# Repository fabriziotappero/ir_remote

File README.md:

# Camera Infrared Remote Control
This repository contains the hardware and software implementation of a infrared 
remote control based on the [Espressif ESP32 module]. This module allow to remotely
control any infrared camera like, in my case, the Sony NEX6 camera.

Notice how an IR reader (U3) can be used to program the ESP32 so that the same
remote can actually control any given camera. 

The schematic and PCB was designed using de EDA tool [KiCad] and all C++ 
code was compiled using the [Espressif ESP32 toolchain].

## Electronic Schematic
![][ir_remote_sch]

[ir_remote_sch]: https://github.com/fabriziotappero/ir_remote/blob/master/PCB/ir_remote_sch.png ""
[Espressif ESP32 module]: https://www.espressif.com/en/products/hardware/development-boards
[Espressif ESP32 toolchain]: https://dl.espressif.com/doc/esp-idf/latest/index.html
[KiCad]: http://kicad-pcb.org/

## Printed Circuit Board
This is the 2 layer PCB designed to sit on top of a ESP32 evaluation board. Notice the castellated
mounting holes.

![][ir_remote_pcb]

[ir_remote_pcb]: https://github.com/fabriziotappero/ir_remote/blob/master/PCB/ir_remote_pcb.png ""

## Hardware And Software Tools

Install **Kicad 5** on Debial-like Linux systems:
```
sudo add-apt-repository --yes ppa:js-reynaud/kicad-5
sudo apt-get update
sudo apt-get install kicad kicad-libraries
```

Install **ESP32 Espressif** compiler with its dependencies:
```
sudo apt-get install git wget make libncurses-dev flex bison gperf python python-serial

wget https://dl.espressif.com/dl/xtensa-esp32-elf-linux64-1.22.0-80-g6c4433a-5.2.0.tar.gz

tar -xvf xtensa-esp32-elf-linux64-1.22.0-80-g6c4433a-5.2.0.tar.gz
sudo mv xtensa-esp32-elf /opt
export PATH=/opt/xtensa-esp32-elf/bin:$PATH
```
Install the **ESP32 Espressif** developing environment IDF:
```
mkdir /opt/eps32 
cd /opt/eps32
git clone --recursive https://github.com/espressif/esp-idf.git
cd esp-idf
git submodule update --init
export IDF_PATH=/opt/esp32/esp-idf
```

Begin from a simple example:
```
git clone https://github.com/espressif/esp-idf-template.git myapp
cd myapp
make menuconfig
make flash
```
A lot of code examples in ```/opt/esp32/esp-idf/examples```. For more information refer to the [Espressif ESP32 Programming Guide]

[Espressif ESP32 Programming Guide]: https://dl.espressif.com/doc/esp-idf/latest/index.html

## References

[Espressif ESP32 Programming Guide](https://dl.espressif.com/doc/esp-idf/latest/index.html)

## More Information
For any enquiry contact:

fabrizio.tappero@gmail.com

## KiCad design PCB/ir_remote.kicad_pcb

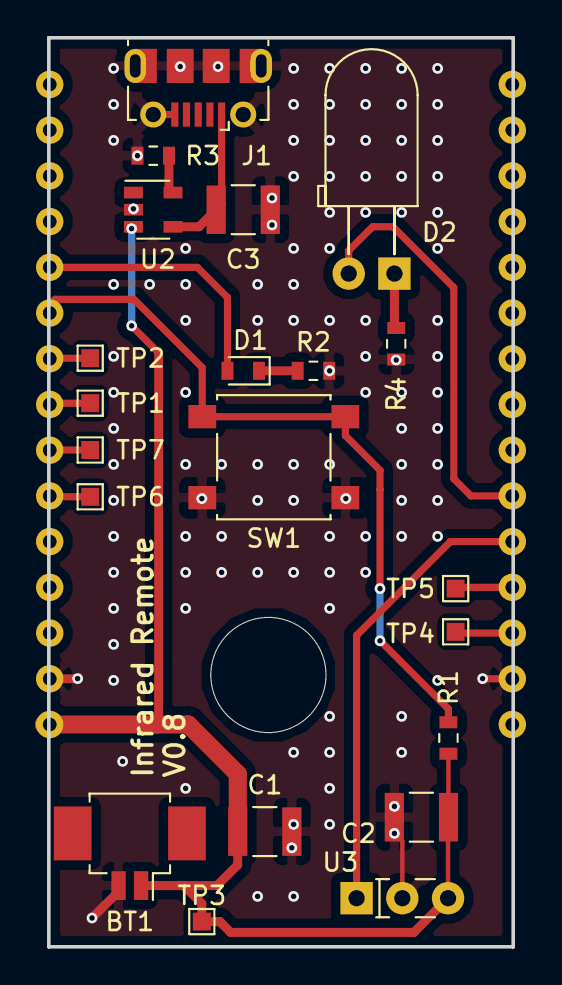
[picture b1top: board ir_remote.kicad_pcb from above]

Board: 2 copper layers, 25.8 x 50.5 mm, 22 parts (1 on the bottom side), 16 nets.

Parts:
BT1: SM02B-SRSS-TB (LF)(SN); Molex_PicoBlade_53261-0271_1x02_P1.25mm_Horizontal
C1, C2, C3: 4.7uF; C_1210_3225Metric
D1: APTD1608LCGCK; LED_0603_1608Metric
D2: 15400394A3590; LED_D5.0mm_Horizontal_O3.81mm_Z3.0mm
J1: 105017-0001; USB_Micro-B_Molex-105017-0001
R1: 10k; R_0603_1608Metric
R2, R3: 2k; R_0603_1608Metric
R4: 120R; R_0603_1608Metric
SW1: 95C06B3GWRT; SW_SPST_B3S-1000
TP1, TP2, TP3, TP4, TP5, TP6, TP7: Test_Point; TestPoint_Pad_1.0x1.0mm
U1: ESP32-DOIT-EVALKIT
U2: MCP73832T2DFI/OT; SOT-23-5
U3: TSOP38238; LED_Rectangular_W5.0mm_H2.0mm-3Pins

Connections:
4V2: BT1.1, C1.1, C2.1, R1.2, TP3.1, U1.30, U2.3, U3.3
GND: BT1.2, C1.2, C2.2, C3.2, J1.5, J1.6, R2.1, R3.1, R4.1, SW1.1, U1.2, U1.29, U2.2, U3.2
unnamed: C3.1, J1.1, U2.4
unnamed: D1.1, R2.2
unnamed: D1.2, U1.20
unnamed: D2.1, R4.2
unnamed: D2.2, U1.6
unnamed: R1.1, SW1.2, U1.21
unnamed: R3.2, U2.5
unnamed: TP1.1, U1.23
unnamed: TP2.1, U1.22
unnamed: TP4.1, U1.3
unnamed: TP5.1, U1.4
unnamed: TP6.1, U1.25
unnamed: TP7.1, U1.24
unnamed: U1.5, U3.1

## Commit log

2018-03-22 added basic github info
2018-03-22 minor
2018-03-23 fixed several 3D components and layout gnd via
